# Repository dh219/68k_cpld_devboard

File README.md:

# 68k_cpld_devboard

A CPLD devboard for the DIP64 68000.

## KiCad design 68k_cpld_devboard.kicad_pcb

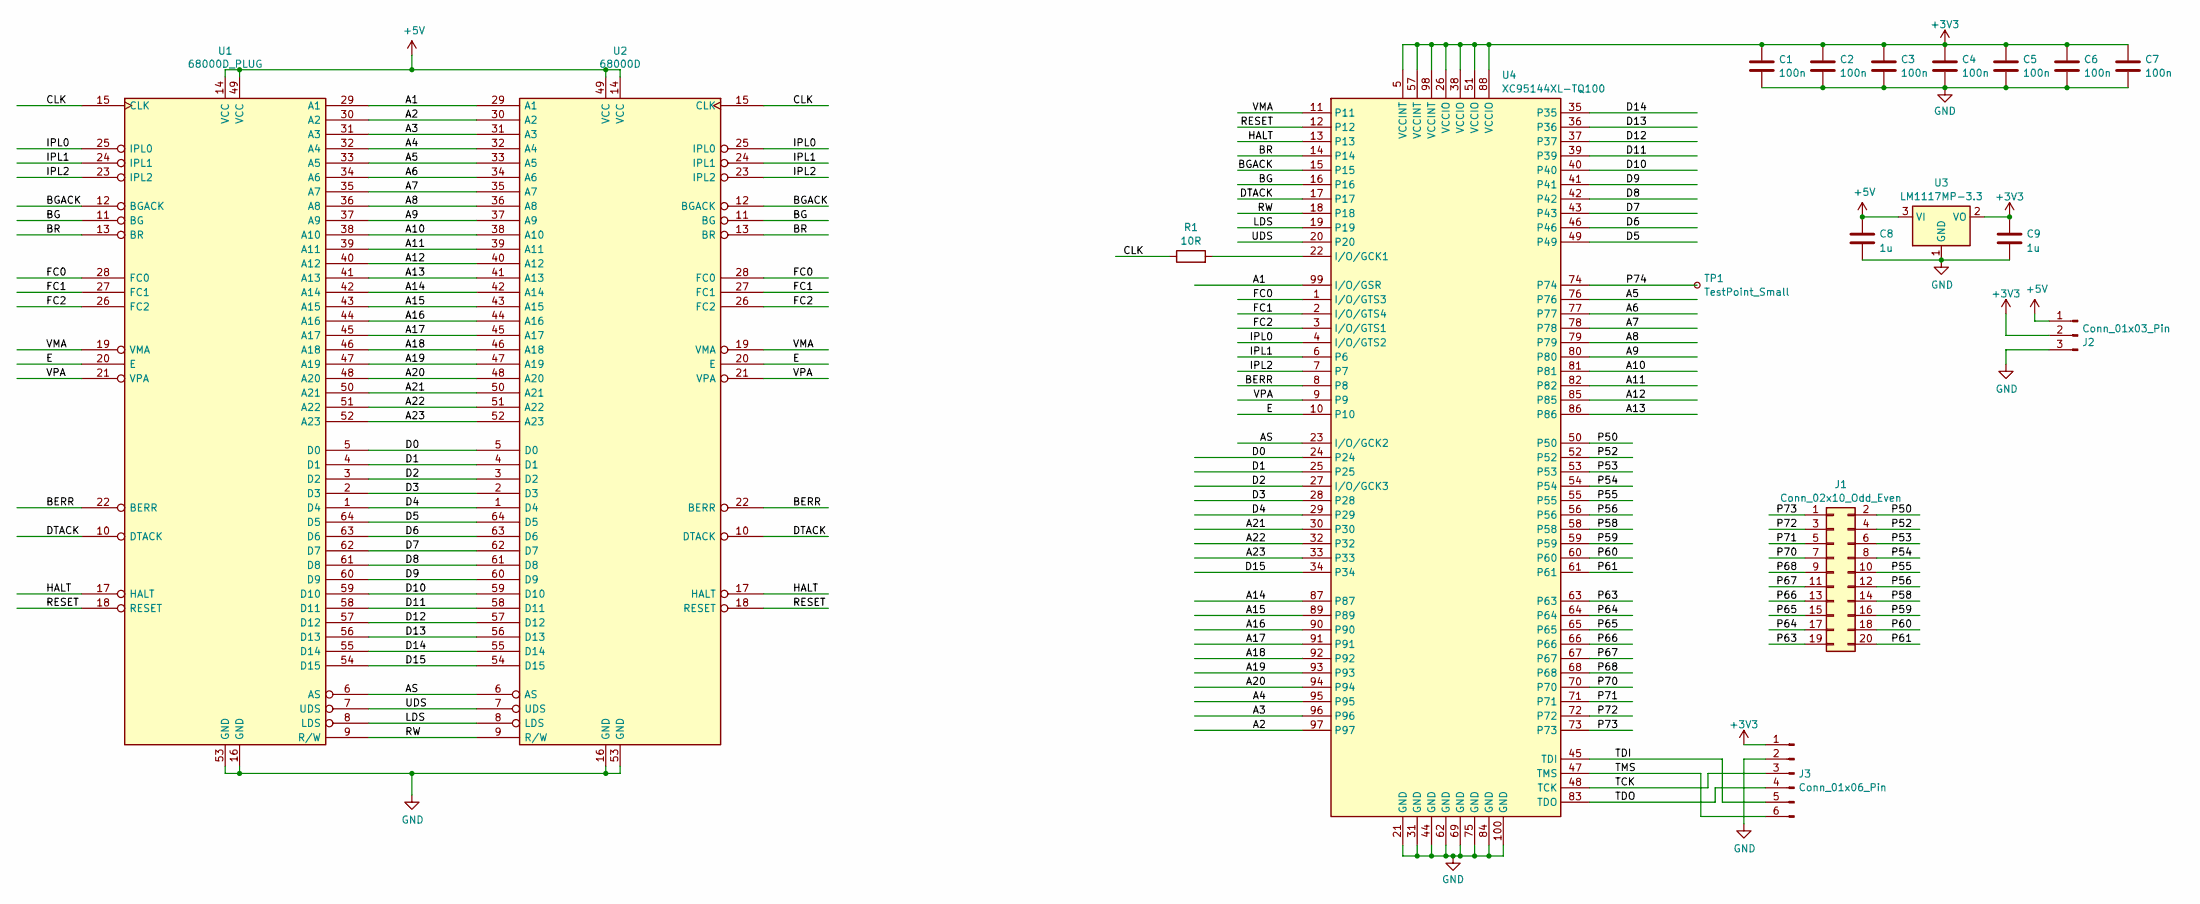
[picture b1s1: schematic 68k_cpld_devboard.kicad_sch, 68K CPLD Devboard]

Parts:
C1, C2, C3, C4, C5, C6, C7: 100n; C_0805_2012Metric_Pad1.18x1.45mm_HandSolder
C8, C9: 1u; C_0805_2012Metric_Pad1.18x1.45mm_HandSolder
J1: Conn_02x10_Odd_Even; PinSocket_2x10_P2.54mm_Vertical
J2: Conn_01x03_Pin; PinHeader_1x03_P2.54mm_Vertical
J3: Conn_01x06_Pin; PinHeader_1x06_P2.54mm_Vertical
R1: 10R; R_0805_2012Metric_Pad1.20x1.40mm_HandSolder
TP1: TestPoint_Small; TestPoint_Pad_D1.0mm
U1: 68000D_PLUG; DIP-64_W22.86mm_LongPads
U2: 68000D; DIP-64_W22.86mm_Socket_LongPads
U3: LM1117MP-3.3; SOT-223-3_TabPin2
U4: XC95144XL-TQ100; TQFP-100_14x14mm_P0.5mm

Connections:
+3V3: C1.1, C2.1, C3.1, C4.1, C5.1, C6.1, C7.1, C9.1, J2.2, J3.1, U3.2 (VO), U4.5 (VCCINT), U4.26 (VCCIO), U4.38 (VCCIO), U4.51 (VCCIO), U4.57 (VCCINT), U4.88 (VCCIO), U4.98 (VCCINT)
+5V: C8.1, J2.1, U1.14 (VCC), U1.49 (VCC), U2.14 (VCC), U2.49 (VCC), U3.3 (VI)
/A1: U1.29 (A1), U2.29 (A1), U4.99 (I/O/GSR)
/A2: U1.30 (A2), U2.30 (A2), U4.97
/A3: U1.31 (A3), U2.31 (A3), U4.96
/A4: U1.32 (A4), U2.32 (A4), U4.95
/A5: U1.33 (A5), U2.33 (A5), U4.76
/A6: U1.34 (A6), U2.34 (A6), U4.77
/A7: U1.35 (A7), U2.35 (A7), U4.78
/A8: U1.36 (A8), U2.36 (A8), U4.79
/A9: U1.37 (A9), U2.37 (A9), U4.80
/A10: U1.38 (A10), U2.38 (A10), U4.81
/A11: U1.39 (A11), U2.39 (A11), U4.82
/A12: U1.40 (A12), U2.40 (A12), U4.85
/A13: U1.41 (A13), U2.41 (A13), U4.86
/A14: U1.42 (A14), U2.42 (A14), U4.87
/A15: U1.43 (A15), U2.43 (A15), U4.89
/A16: U1.44 (A16), U2.44 (A16), U4.90
/A17: U1.45 (A17), U2.45 (A17), U4.91
/A18: U1.46 (A18), U2.46 (A18), U4.92
/A19: U1.47 (A19), U2.47 (A19), U4.93
/A20: U1.48 (A20), U2.48 (A20), U4.94
/A21: U1.50 (A21), U2.50 (A21), U4.30
/A22: U1.51 (A22), U2.51 (A22), U4.32
/A23: U1.52 (A23), U2.52 (A23), U4.33
/AS: U1.6 (AS), U2.6 (AS), U4.23 (I/O/GCK2)
/BERR: U1.22 (BERR), U2.22 (BERR), U4.8
/BG: U1.11 (BG), U2.11 (BG), U4.16
/BGACK: U1.12 (BGACK), U2.12 (BGACK), U4.15
/BR: U1.13 (BR), U2.13 (BR), U4.14
/CLK: R1.1, U1.15 (CLK), U2.15 (CLK)
/D0: U1.5 (D0), U2.5 (D0), U4.24
/D1: U1.4 (D1), U2.4 (D1), U4.25
/D2: U1.3 (D2), U2.3 (D2), U4.27 (I/O/GCK3)
/D3: U1.2 (D3), U2.2 (D3), U4.28
/D4: U1.1 (D4), U2.1 (D4), U4.29
/D5: U1.64 (D5), U2.64 (D5), U4.49
/D6: U1.63 (D6), U2.63 (D6), U4.46
/D7: U1.62 (D7), U2.62 (D7), U4.43
/D8: U1.61 (D8), U2.61 (D8), U4.42
/D9: U1.60 (D9), U2.60 (D9), U4.41
/D10: U1.59 (D10), U2.59 (D10), U4.40
/D11: U1.58 (D11), U2.58 (D11), U4.39
/D12: U1.57 (D12), U2.57 (D12), U4.37
/D13: U1.56 (D13), U2.56 (D13), U4.36
/D14: U1.55 (D14), U2.55 (D14), U4.35
/D15: U1.54 (D15), U2.54 (D15), U4.34
/DTACK: U1.10 (DTACK), U2.10 (DTACK), U4.17
/E: U1.20 (E), U2.20 (E), U4.10
/FC0: U1.28 (FC0), U2.28 (FC0), U4.1 (I/O/GTS3)
/FC1: U1.27 (FC1), U2.27 (FC1), U4.2 (I/O/GTS4)
/FC2: U1.26 (FC2), U2.26 (FC2), U4.3 (I/O/GTS1)
/HALT: U1.17 (HALT), U2.17 (HALT), U4.13
/IPL0: U1.25 (IPL0), U2.25 (IPL0), U4.4 (I/O/GTS2)
/IPL1: U1.24 (IPL1), U2.24 (IPL1), U4.6
/IPL2: U1.23 (IPL2), U2.23 (IPL2), U4.7
/LDS: U1.8 (LDS), U2.8 (LDS), U4.19
/P50: J1.2, U4.50
/P52: J1.4, U4.52
/P53: J1.6, U4.53
/P54: J1.8, U4.54
/P55: J1.10, U4.55
/P56: J1.12, U4.56
/P58: J1.14, U4.58
/P59: J1.16, U4.59
/P60: J1.18, U4.60
/P61: J1.20, U4.61
/P63: J1.19, U4.63
/P64: J1.17, U4.64
/P65: J1.15, U4.65
/P66: J1.13, U4.66
/P67: J1.11, U4.67
/P68: J1.9, U4.68
/P70: J1.7, U4.70
/P71: J1.5, U4.71
/P72: J1.3, U4.72
/P73: J1.1, U4.73
/P74: TP1.1, U4.74
/RESET: U1.18 (RESET), U2.18 (RESET), U4.12
/RW: U1.9 (R/W), U2.9 (R/W), U4.18
/TCK: J3.3, U4.48 (TCK)
/TDI: J3.5, U4.45 (TDI)
/TDO: J3.4, U4.83 (TDO)
/TMS: J3.6, U4.47 (TMS)
/UDS: U1.7 (UDS), U2.7 (UDS), U4.20
/VMA: U1.19 (VMA), U2.19 (VMA), U4.11
/VPA: U1.21 (VPA), U2.21 (VPA), U4.9
GND: C1.2, C2.2, C3.2, C4.2, C5.2, C6.2, C7.2, C8.2, C9.2, J2.3, J3.2, U1.16 (GND), U1.53 (GND), U2.16 (GND), U2.53 (GND), U3.1 (GND), U4.21 (GND), U4.31 (GND), U4.44 (GND), U4.62 (GND), U4.69 (GND), U4.75 (GND), U4.84 (GND), U4.100 (GND)
unnamed: R1.2, U4.22 (I/O/GCK1)

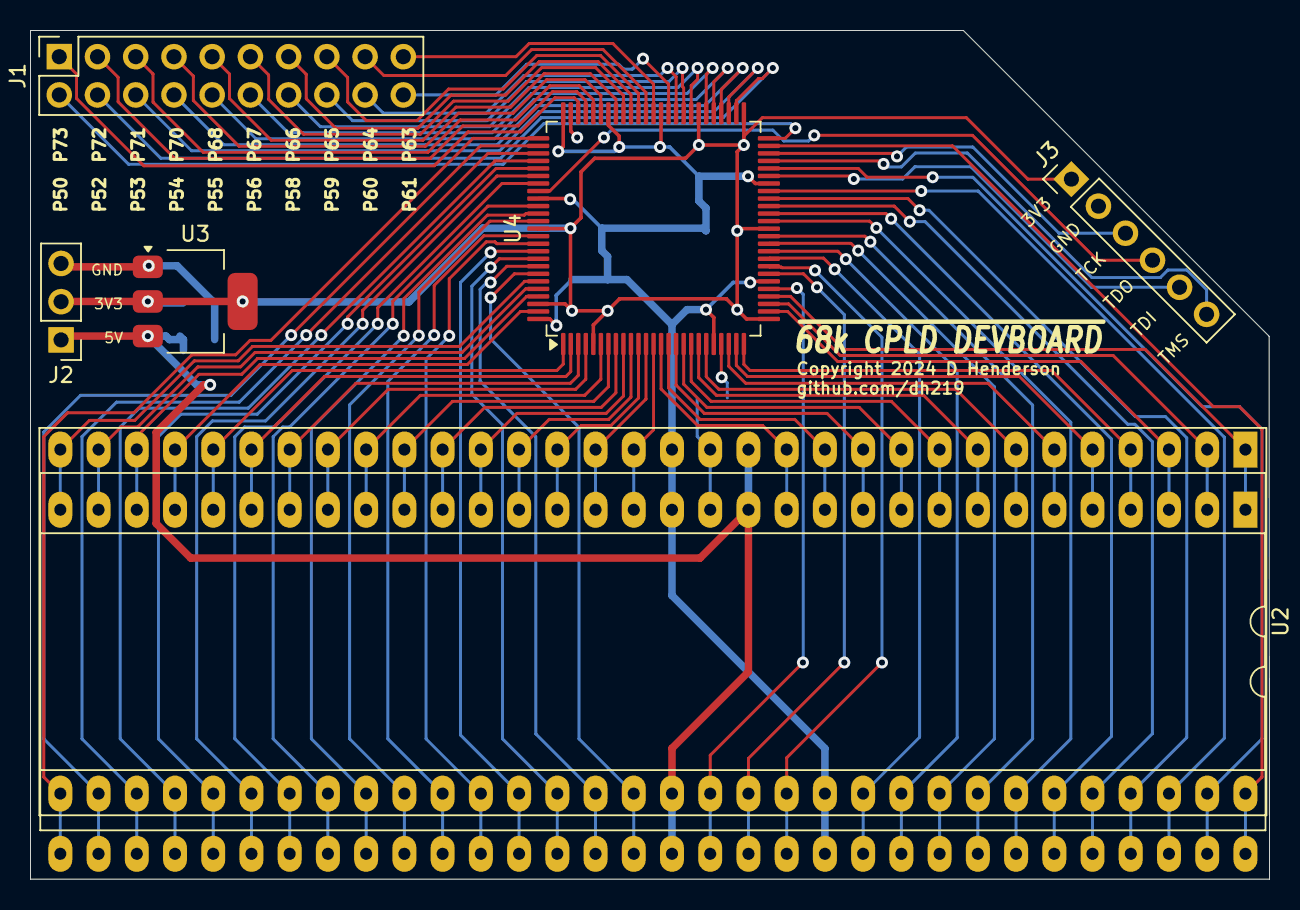
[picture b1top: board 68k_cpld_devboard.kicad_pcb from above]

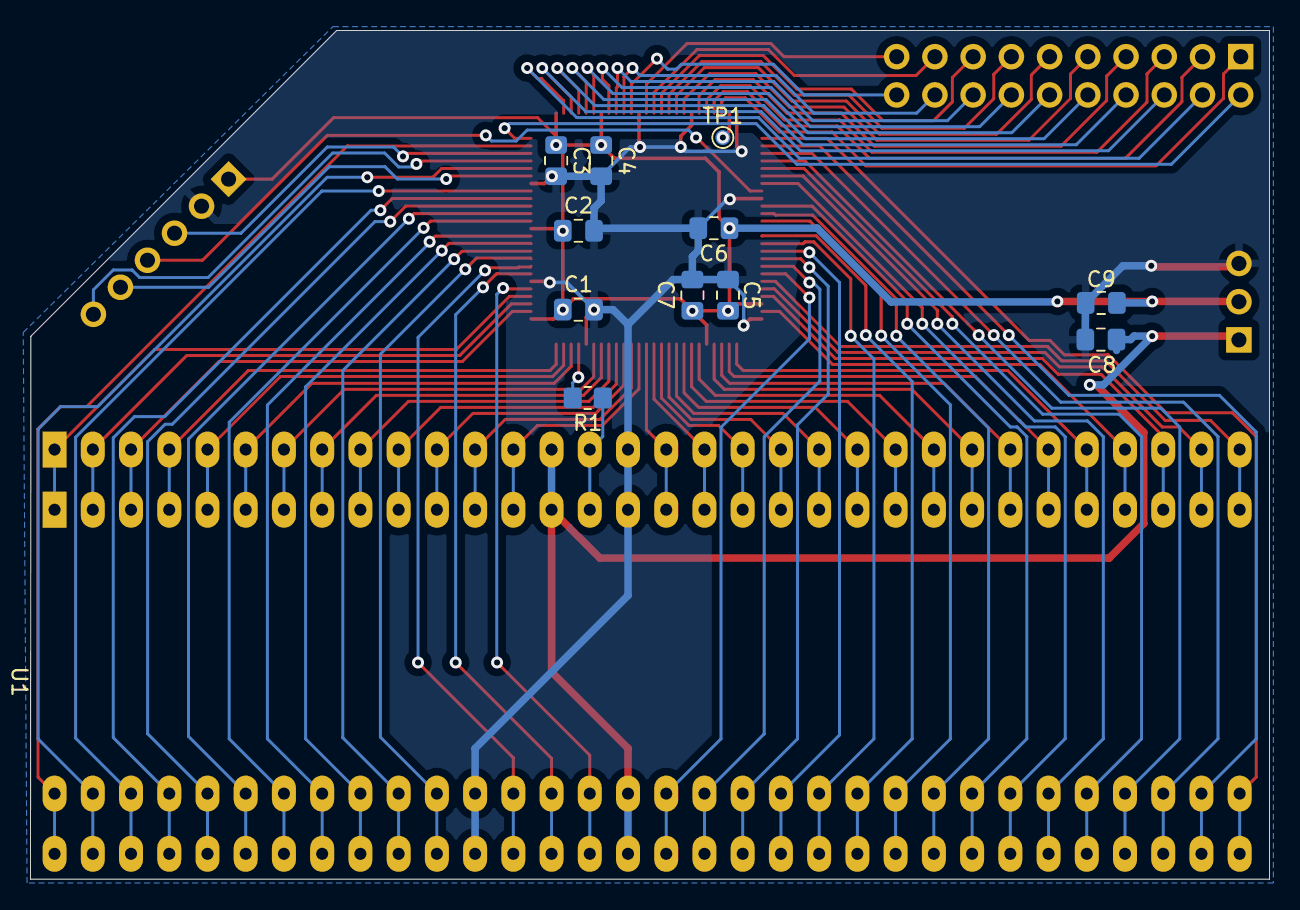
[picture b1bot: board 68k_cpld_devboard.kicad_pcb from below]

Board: 2 copper layers, 82.3 x 56.4 mm, 18 parts (11 on the bottom side), 89 nets.

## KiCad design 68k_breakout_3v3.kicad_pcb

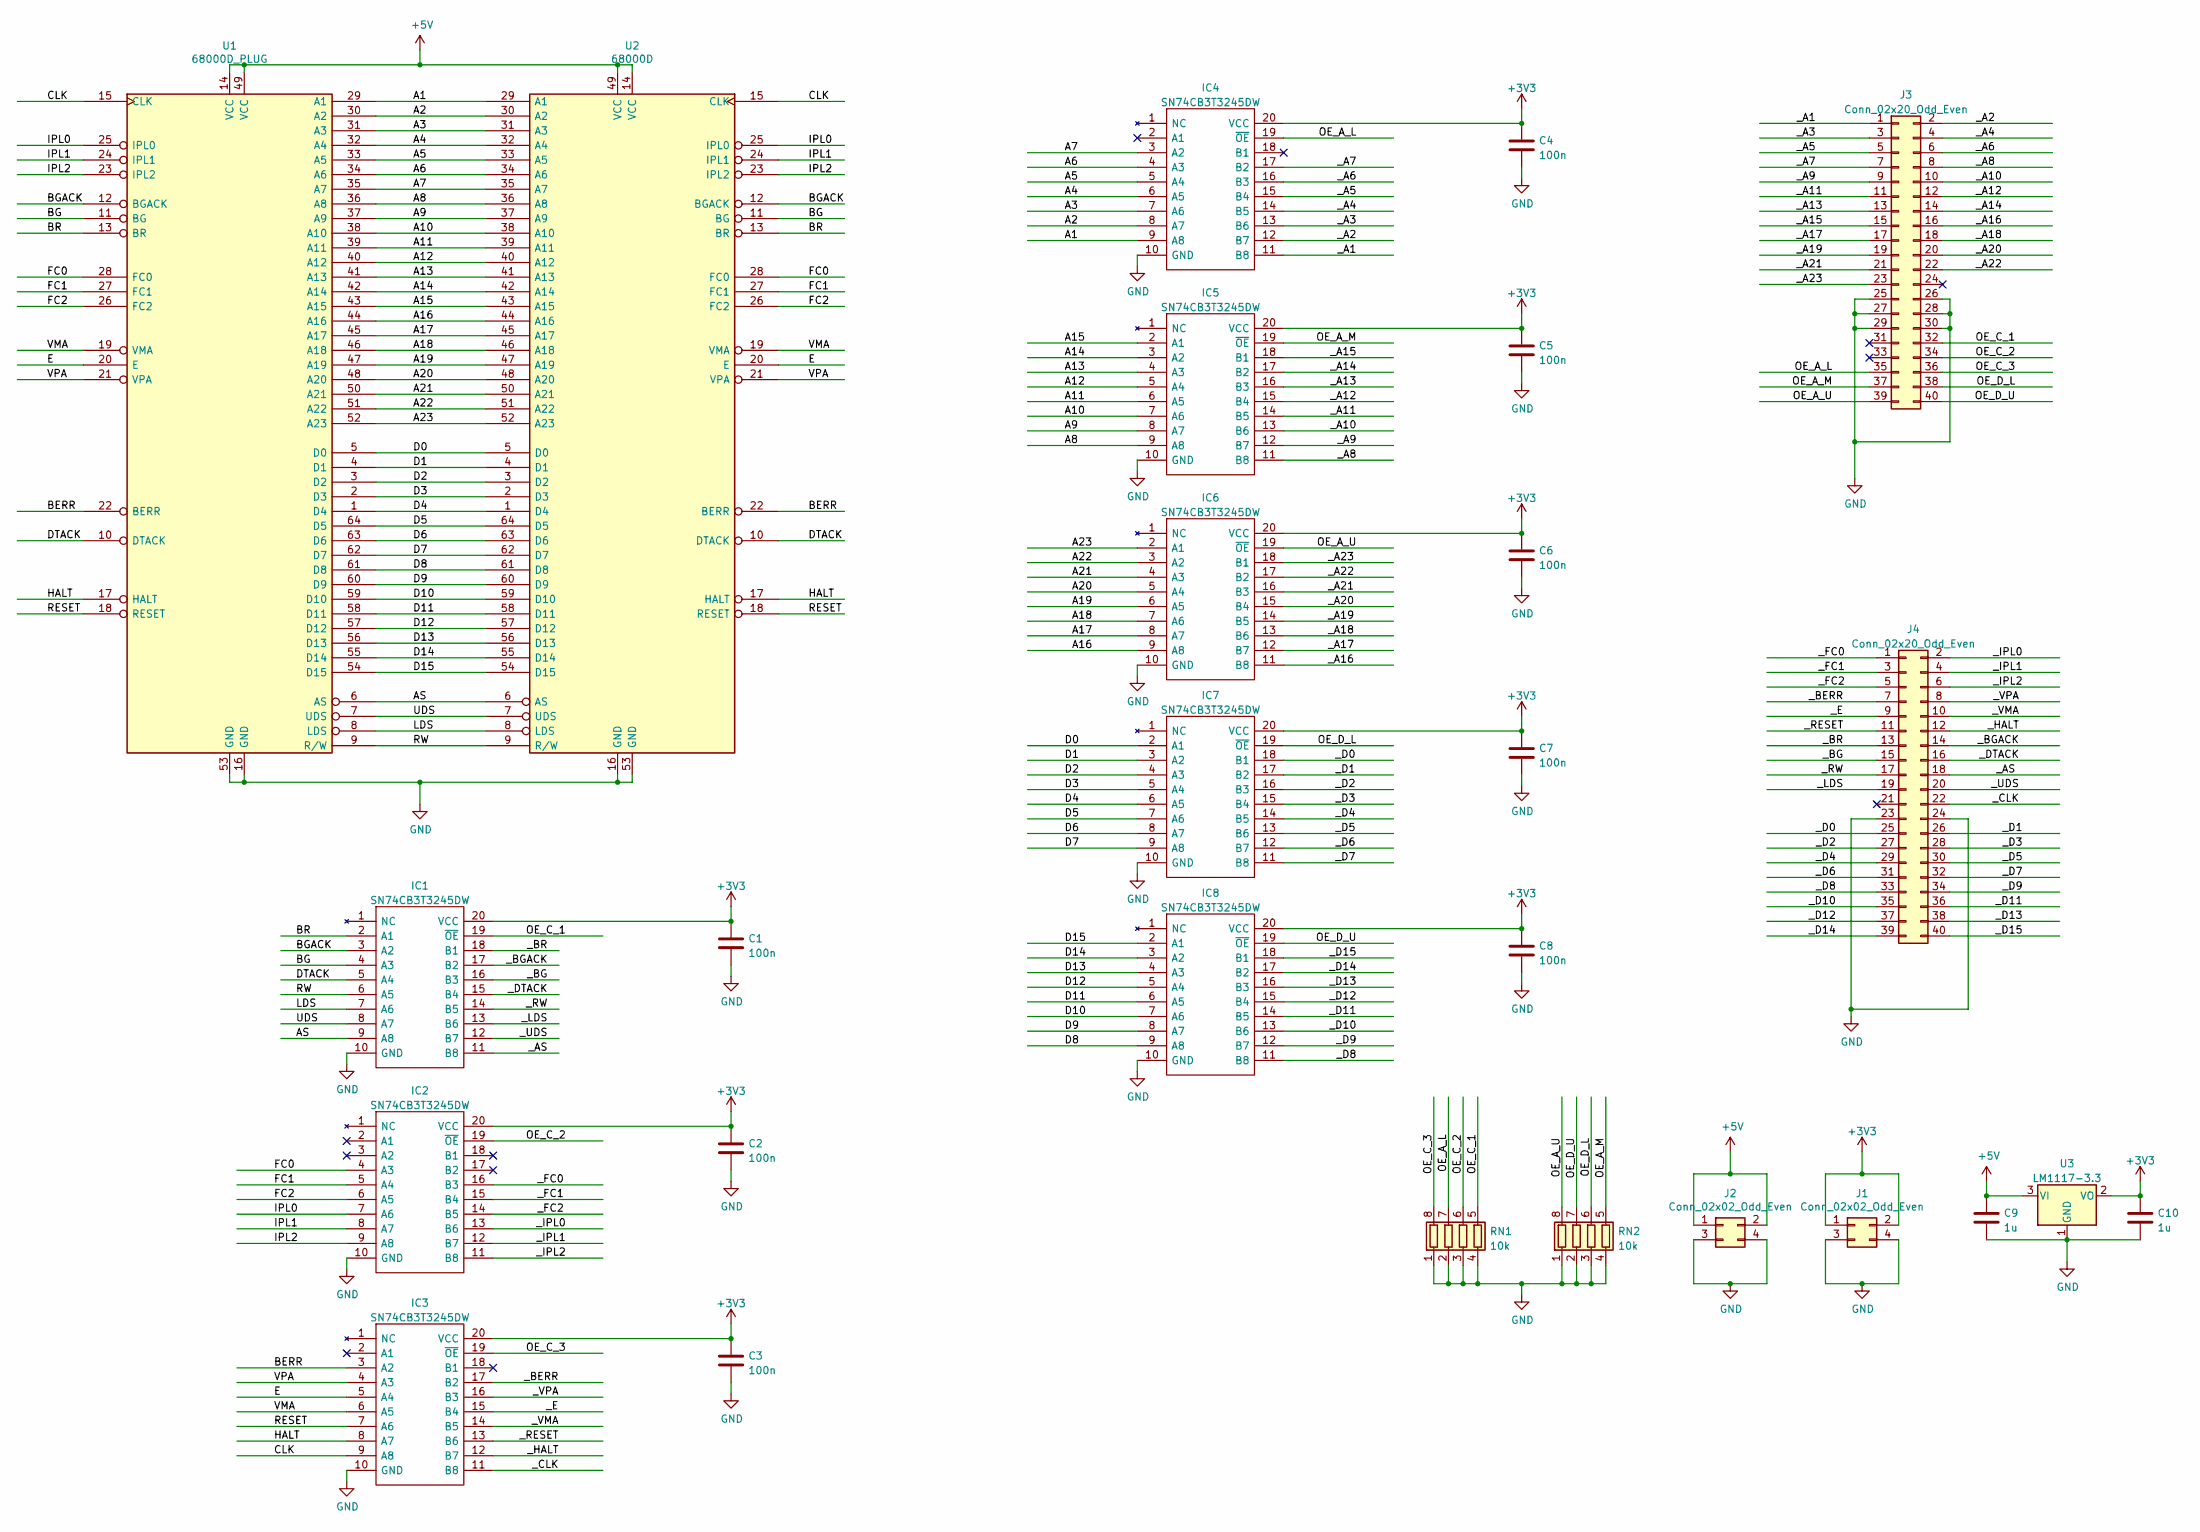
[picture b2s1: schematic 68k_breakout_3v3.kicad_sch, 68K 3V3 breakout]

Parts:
C1, C2, C3, C4, C5, C6, C7, C8: 100n; C_0805_2012Metric_Pad1.18x1.45mm_HandSolder
C9, C10: 1u; C_0805_2012Metric_Pad1.18x1.45mm_HandSolder
IC1, IC2, IC3, IC4, IC5, IC6, IC7, IC8: SN74CB3T3245DW; TSSOP-20_4.4x6.5mm_P0.65mm; Manufacturer_Part_Number SN74CB3T3245DW; Mouser Part Number 595-SN74CB3T3245DW
J1, J2: Conn_02x02_Odd_Even; PinSocket_2x02_P2.54mm_Vertical
J3, J4: Conn_02x20_Odd_Even; PinHeader_2x20_P2.54mm_Vertical
RN1, RN2: 10k; R_Array_Convex_4x0603
U1: 68000D_PLUG; DIP-64_W22.86mm_LongPads
U2: 68000D; DIP-64_W22.86mm_Socket_LongPads
U3: LM1117-3.3; SOT-223-3_TabPin2

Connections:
+3V3: C1.1, C2.1, C3.1, C4.1, C5.1, C6.1, C7.1, C8.1, C10.1, IC1.20 (VCC), IC2.20 (VCC), IC3.20 (VCC), IC4.20 (VCC), IC5.20 (VCC), IC6.20 (VCC), IC7.20 (VCC), IC8.20 (VCC), J1.1, J1.2, U3.2 (VO)
+5V: C9.1, J2.1, J2.2, U1.14 (VCC), U1.49 (VCC), U2.14 (VCC), U2.49 (VCC), U3.3 (VI)
/A1: IC4.9 (A8), U1.29 (A1), U2.29 (A1)
/A2: IC4.8 (A7), U1.30 (A2), U2.30 (A2)
/A3: IC4.7 (A6), U1.31 (A3), U2.31 (A3)
/A4: IC4.6 (A5), U1.32 (A4), U2.32 (A4)
/A5: IC4.5 (A4), U1.33 (A5), U2.33 (A5)
/A6: IC4.4 (A3), U1.34 (A6), U2.34 (A6)
/A7: IC4.3 (A2), U1.35 (A7), U2.35 (A7)
/A8: IC5.9 (A8), U1.36 (A8), U2.36 (A8)
/A9: IC5.8 (A7), U1.37 (A9), U2.37 (A9)
/A10: IC5.7 (A6), U1.38 (A10), U2.38 (A10)
/A11: IC5.6 (A5), U1.39 (A11), U2.39 (A11)
/A12: IC5.5 (A4), U1.40 (A12), U2.40 (A12)
/A13: IC5.4 (A3), U1.41 (A13), U2.41 (A13)
/A14: IC5.3 (A2), U1.42 (A14), U2.42 (A14)
/A15: IC5.2 (A1), U1.43 (A15), U2.43 (A15)
/A16: IC6.9 (A8), U1.44 (A16), U2.44 (A16)
/A17: IC6.8 (A7), U1.45 (A17), U2.45 (A17)
/A18: IC6.7 (A6), U1.46 (A18), U2.46 (A18)
/A19: IC6.6 (A5), U1.47 (A19), U2.47 (A19)
/A20: IC6.5 (A4), U1.48 (A20), U2.48 (A20)
/A21: IC6.4 (A3), U1.50 (A21), U2.50 (A21)
/A22: IC6.3 (A2), U1.51 (A22), U2.51 (A22)
/A23: IC6.2 (A1), U1.52 (A23), U2.52 (A23)
/AS: IC1.9 (A8), U1.6 (AS), U2.6 (AS)
/BERR: IC3.3 (A2), U1.22 (BERR), U2.22 (BERR)
/BG: IC1.4 (A3), U1.11 (BG), U2.11 (BG)
/BGACK: IC1.3 (A2), U1.12 (BGACK), U2.12 (BGACK)
/BR: IC1.2 (A1), U1.13 (BR), U2.13 (BR)
/CLK: IC3.9 (A8), U1.15 (CLK), U2.15 (CLK)
/D0: IC7.2 (A1), U1.5 (D0), U2.5 (D0)
/D1: IC7.3 (A2), U1.4 (D1), U2.4 (D1)
/D2: IC7.4 (A3), U1.3 (D2), U2.3 (D2)
/D3: IC7.5 (A4), U1.2 (D3), U2.2 (D3)
/D4: IC7.6 (A5), U1.1 (D4), U2.1 (D4)
/D5: IC7.7 (A6), U1.64 (D5), U2.64 (D5)
/D6: IC7.8 (A7), U1.63 (D6), U2.63 (D6)
/D7: IC7.9 (A8), U1.62 (D7), U2.62 (D7)
/D8: IC8.9 (A8), U1.61 (D8), U2.61 (D8)
/D9: IC8.8 (A7), U1.60 (D9), U2.60 (D9)
/D10: IC8.7 (A6), U1.59 (D10), U2.59 (D10)
/D11: IC8.6 (A5), U1.58 (D11), U2.58 (D11)
/D12: IC8.5 (A4), U1.57 (D12), U2.57 (D12)
/D13: IC8.4 (A3), U1.56 (D13), U2.56 (D13)
/D14: IC8.3 (A2), U1.55 (D14), U2.55 (D14)
/D15: IC8.2 (A1), U1.54 (D15), U2.54 (D15)
/DTACK: IC1.5 (A4), U1.10 (DTACK), U2.10 (DTACK)
/E: IC3.5 (A4), U1.20 (E), U2.20 (E)
/FC0: IC2.4 (A3), U1.28 (FC0), U2.28 (FC0)
/FC1: IC2.5 (A4), U1.27 (FC1), U2.27 (FC1)
/FC2: IC2.6 (A5), U1.26 (FC2), U2.26 (FC2)
/HALT: IC3.8 (A7), U1.17 (HALT), U2.17 (HALT)
/IPL0: IC2.7 (A6), U1.25 (IPL0), U2.25 (IPL0)
/IPL1: IC2.8 (A7), U1.24 (IPL1), U2.24 (IPL1)
/IPL2: IC2.9 (A8), U1.23 (IPL2), U2.23 (IPL2)
/LDS: IC1.7 (A6), U1.8 (LDS), U2.8 (LDS)
/OE_A_L: IC4.19 (~OE), J3.35, RN1.7 (R2.2)
/OE_A_M: IC5.19 (~OE), J3.37, RN2.5 (R4.2)
/OE_A_U: IC6.19 (~OE), J3.39, RN2.8 (R1.2)
/OE_C_1: IC1.19 (~OE), J3.32, RN1.5 (R4.2)
/OE_C_2: IC2.19 (~OE), J3.34, RN1.6 (R3.2)
/OE_C_3: IC3.19 (~OE), J3.36, RN1.8 (R1.2)
/OE_D_L: IC7.19 (~OE), J3.38, RN2.6 (R3.2)
/OE_D_U: IC8.19 (~OE), J3.40, RN2.7 (R2.2)
/RESET: IC3.7 (A6), U1.18 (RESET), U2.18 (RESET)
/RW: IC1.6 (A5), U1.9 (R/W), U2.9 (R/W)
/UDS: IC1.8 (A7), U1.7 (UDS), U2.7 (UDS)
/VMA: IC3.6 (A5), U1.19 (VMA), U2.19 (VMA)
/VPA: IC3.4 (A3), U1.21 (VPA), U2.21 (VPA)
/_A1: IC4.11 (B8), J3.1
/_A2: IC4.12 (B7), J3.2
/_A3: IC4.13 (B6), J3.3
/_A4: IC4.14 (B5), J3.4
/_A5: IC4.15 (B4), J3.5
/_A6: IC4.16 (B3), J3.6
/_A7: IC4.17 (B2), J3.7
/_A8: IC5.11 (B8), J3.8
/_A9: IC5.12 (B7), J3.9
/_A10: IC5.13 (B6), J3.10
/_A11: IC5.14 (B5), J3.11
/_A12: IC5.15 (B4), J3.12
/_A13: IC5.16 (B3), J3.13
/_A14: IC5.17 (B2), J3.14
/_A15: IC5.18 (B1), J3.15
/_A16: IC6.11 (B8), J3.16
/_A17: IC6.12 (B7), J3.17
/_A18: IC6.13 (B6), J3.18
/_A19: IC6.14 (B5), J3.19
/_A20: IC6.15 (B4), J3.20
/_A21: IC6.16 (B3), J3.21
/_A22: IC6.17 (B2), J3.22
/_A23: IC6.18 (B1), J3.23
/_AS: IC1.11 (B8), J4.18
/_BERR: IC3.17 (B2), J4.7
/_BG: IC1.16 (B3), J4.15
/_BGACK: IC1.17 (B2), J4.14
/_BR: IC1.18 (B1), J4.13
/_CLK: IC3.11 (B8), J4.22
/_D0: IC7.18 (B1), J4.25
/_D1: IC7.17 (B2), J4.26
/_D2: IC7.16 (B3), J4.27
/_D3: IC7.15 (B4), J4.28
/_D4: IC7.14 (B5), J4.29
/_D5: IC7.13 (B6), J4.30
/_D6: IC7.12 (B7), J4.31
/_D7: IC7.11 (B8), J4.32
/_D8: IC8.11 (B8), J4.33
/_D9: IC8.12 (B7), J4.34
/_D10: IC8.13 (B6), J4.35
/_D11: IC8.14 (B5), J4.36
/_D12: IC8.15 (B4), J4.37
/_D13: IC8.16 (B3), J4.38
/_D14: IC8.17 (B2), J4.39
/_D15: IC8.18 (B1), J4.40
/_DTACK: IC1.15 (B4), J4.16
/_E: IC3.15 (B4), J4.9
/_FC0: IC2.16 (B3), J4.1
/_FC1: IC2.15 (B4), J4.3
/_FC2: IC2.14 (B5), J4.5
/_HALT: IC3.12 (B7), J4.12
/_IPL0: IC2.13 (B6), J4.2
/_IPL1: IC2.12 (B7), J4.4
/_IPL2: IC2.11 (B8), J4.6
/_LDS: IC1.13 (B6), J4.19
/_RESET: IC3.13 (B6), J4.11
/_RW: IC1.14 (B5), J4.17
/_UDS: IC1.12 (B7), J4.20
/_VMA: IC3.14 (B5), J4.10
/_VPA: IC3.16 (B3), J4.8
GND: C1.2, C2.2, C3.2, C4.2, C5.2, C6.2, C7.2, C8.2, C9.2, C10.2, IC1.10 (GND), IC2.10 (GND), IC3.10 (GND), IC4.10 (GND), IC5.10 (GND), IC6.10 (GND), IC7.10 (GND), IC8.10 (GND), J1.3, J1.4, J2.3, J2.4, J3.25, J3.26, J3.27, J3.28, J3.29, J3.30, J4.23, J4.24, RN1.1 (R1.1), RN1.2 (R2.1), RN1.3 (R3.1), RN1.4 (R4.1), RN2.1 (R1.1), RN2.2 (R2.1), RN2.3 (R3.1), RN2.4 (R4.1), U1.16 (GND), U1.53 (GND), U2.16 (GND), U2.53 (GND), U3.1 (GND)

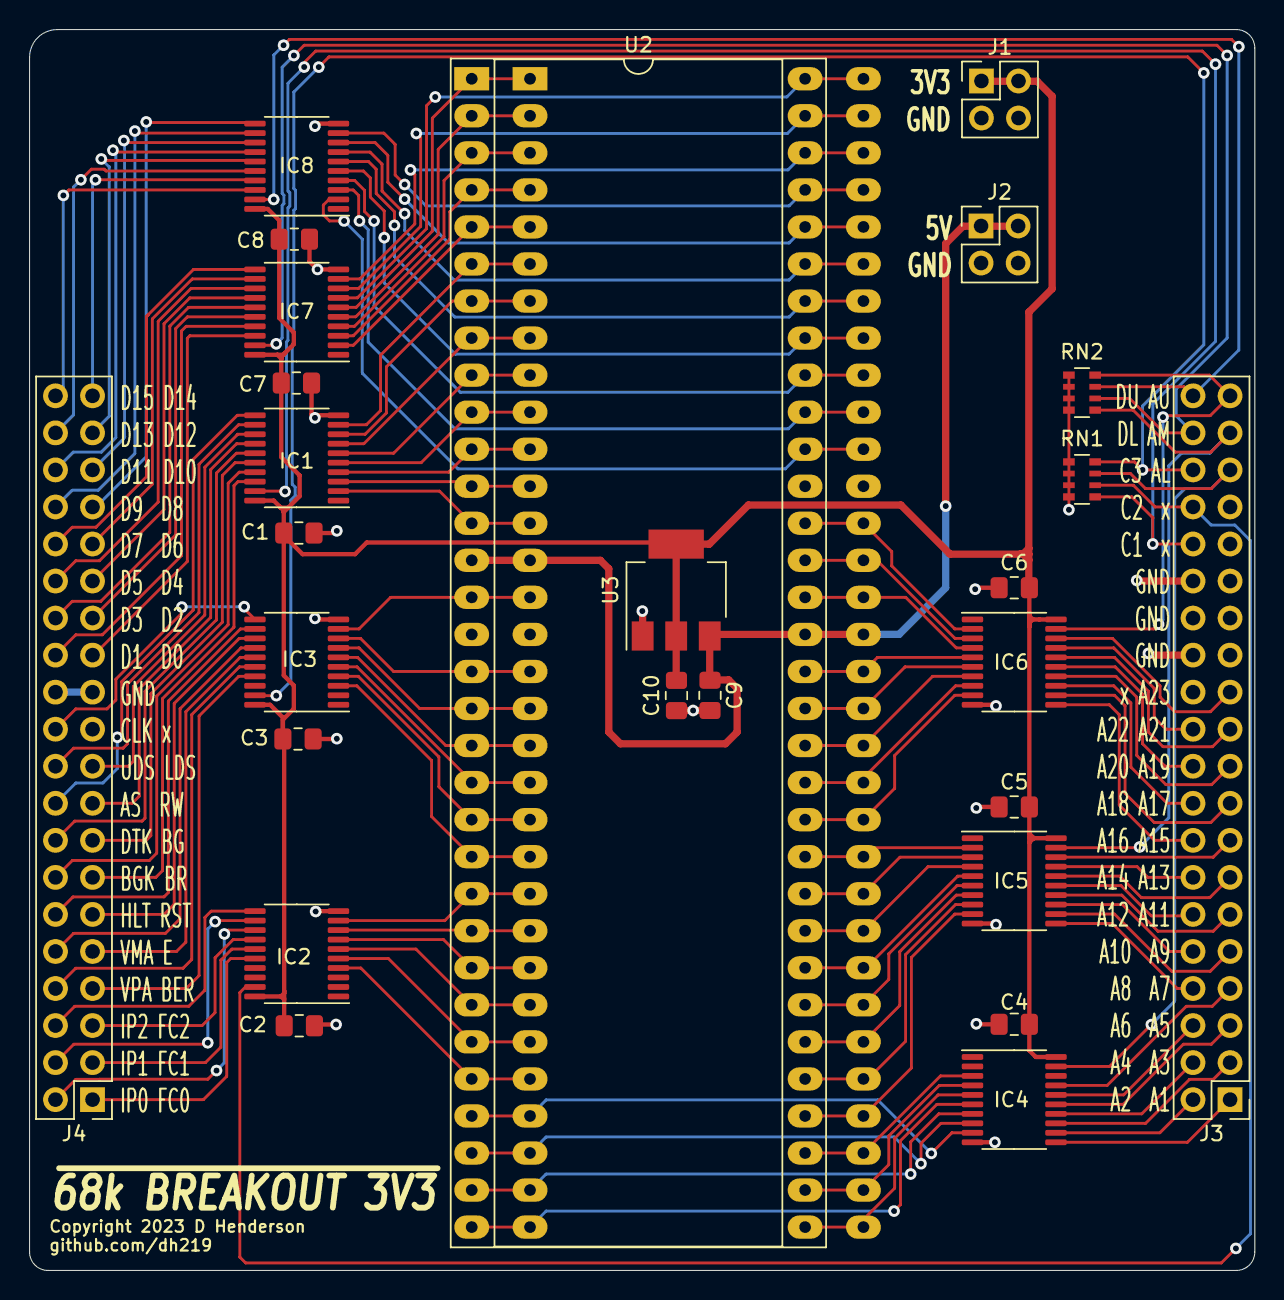
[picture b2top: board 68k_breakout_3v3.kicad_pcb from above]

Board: 2 copper layers, 84.0 x 85.1 mm, 27 parts (0 on the bottom side), 131 nets.

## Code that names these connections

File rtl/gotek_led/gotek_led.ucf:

NET	CLK	LOC = "22";
		
NET	RESET	LOC = "12";
NET	HALT	LOC = "13";

NET	BR	LOC = "14";
NET	BG	LOC = "16";
NET	BGACK	LOC = "15";
		
NET	FC<0>	LOC = "1";
NET	FC<1>	LOC = "2";
NET	FC<2>	LOC = "3";
		
NET	RW	LOC = "18";
NET	AS	LOC = "23";
NET	LDS	LOC = "19";
NET	UDS	LOC = "20";
NET	DTACK	LOC = "17";
NET	BERR	LOC = "8";
		
NET	IPL<0>	LOC = "4";
NET	IPL<1>	LOC = "6";
NET	IPL<2>	LOC = "7";
		
NET	VPA	LOC = "9";
NET	VMA	LOC = "11";
NET	E	LOC = "10";

NET	TP1	LOC = "74";
		
NET	P50	LOC = "50";
		
NET	P52	LOC = "52";
NET	P53	LOC = "53";
NET	P54	LOC = "54";
NET	P55	LOC = "55";
NET	P56	LOC = "56";
		
NET	P58	LOC = "58";
NET	P59	LOC = "59";
NET	P60	LOC = "60";
NET	P61	LOC = "61";
		
NET	P63	LOC = "63";
NET	P64	LOC = "64";
NET	P65	LOC = "65";
NET	P66	LOC = "66";
NET	P67	LOC = "67";
NET	P68	LOC = "68";
		
NET	P70	LOC = "70";
NET	P71	LOC = "71";
NET	P72	LOC = "72";
NET	P73	LOC = "73";
		
		
NET	A<1>	LOC = "99";
NET	A<2>	LOC = "97";
NET	A<3>	LOC = "96";
NET	A<4>	LOC = "95";
NET	A<5>	LOC = "76";
NET	A<6>	LOC = "77";
NET	A<7>	LOC = "78";
NET	A<8>	LOC = "79";
NET	A<9>	LOC = "80";
NET	A<10>	LOC = "81";
NET	A<11>	LOC = "82";
NET	A<12>	LOC = "85";
NET	A<13>	LOC = "86";
NET	A<14>	LOC = "87";
NET	A<15>	LOC = "89";
NET	A<16>	LOC = "90";
NET	A<17>	LOC = "91";
NET	A<18>	LOC = "92";
NET	A<19>	LOC = "93";
NET	A<20>	LOC = "94";
NET	A<21>	LOC = "30";
NET	A<22>	LOC = "32";
NET	A<23>	LOC = "33";
		
NET	D<0>	LOC = "24";
NET	D<1>	LOC = "25";
NET	D<2>	LOC = "27";
NET	D<3>	LOC = "28";
NET	D<4>	LOC = "29";
NET	D<5>	LOC = "49";
NET	D<6>	LOC = "46";
NET	D<7>	LOC = "43";
NET	D<8>	LOC = "42";
NET	D<9>	LOC = "41";
NET	D<10>	LOC = "40";
NET	D<11>	LOC = "39";
NET	D<12>	LOC = "37";
NET	D<13>	LOC = "36";
NET	D<14>	LOC = "35";
NET	D<15>	LOC = "34";

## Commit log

2023-10-26 Initial start of project, copied from 68k_debug
2023-10-30 Initial layout complete
2023-10-31 Tweaked layout to better fit. Passes DRC
2023-10-31 Adding copyright
2023-10-31 Minor tweaks pre-gerberisation
2023-11-11 Removed PRL file
2024-09-12 Started conversion of the old project to a CPLD breakout board
2024-09-12 Passing DRC
2024-09-12 Rev 1 ordered
2024-10-03 Starting point Verilog project that simply sets all pins bar TP1 as input. TP1 is driven to ground.
2024-10-06 TOS206 decoder example with totem-pole CE line.
2024-10-08 Experimental LED display demo starting
2024-10-09 Fixing UCF files
2024-10-09 Starting picovid branch
2024-10-11 Almost working data exchange (slow and loses sync)
2024-10-15 Basic address-driven transfer working, but no speed optimisation
2024-10-18 Current approach not quick enough. Will experiemtn with some PIO techniques.
2024-10-26 sniffing working at 8MHz but no uds/lds discrimination and without resynchronisation
2024-10-27 reasonably reliably write sniffing although state machine doesn't need to wait for AS to go high any more.
2024-12-12 Communication now working semi-reliably. Work at software end needed now. See 47a0682c7aac7dd50775228d36c1d17a406593ef on pico playground
2024-12-12 UDS/LDS mistake. Hopefully better now.
2024-12-20 Cleaning up naming of the ds_in register to avoid confusion.
2025-01-07 DTACK for our new register F1DDB1
2025-01-10 Changed register to word width
2025-01-23 Expanding the register area for future use
2025-04-26 Initial bringup of proper DDB1 board -- not fully working yet
2025-04-28 Had to use TP4 to qualify accesses to memory because I hadn't realised the shifter was on the 'wrong' side of the memory buffers. Also added mode change reset timer.
2025-05-03 line in the sand with an 'alt reg' in reserved low ram. Going to try to sniff shifter writes now
2025-09-28 Image stabilised with MMUBoard added and TP4 used for the Vsync, but refresh is poor. Need to work on pico firmware again next.
2025-09-29 Trying to enable support for two capture modes
2025-10-01 Trying hard to get normal write-sniffing to work, but corrupt transfers.
2025-10-02 After much fighting, write sniffing seems to be almost working again (even blanking again a problem)
2025-10-02 Getting closer -- too many dropped writes, but can actually see some output again.
2025-10-05 Data capture still not working properly
2025-10-07 Still experimenting with timings -- relying on LOAD not sufficient indicator of the memory bus state?
2025-10-08 Working once again on the bus sniffing branch with new WDAT line triggering

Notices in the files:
68k_breakout_3v3.kicad_pcb:
Copyright 2023 D Henderson
68k_cpld_devboard.kicad_pcb:
Copyright 2024 D Henderson
